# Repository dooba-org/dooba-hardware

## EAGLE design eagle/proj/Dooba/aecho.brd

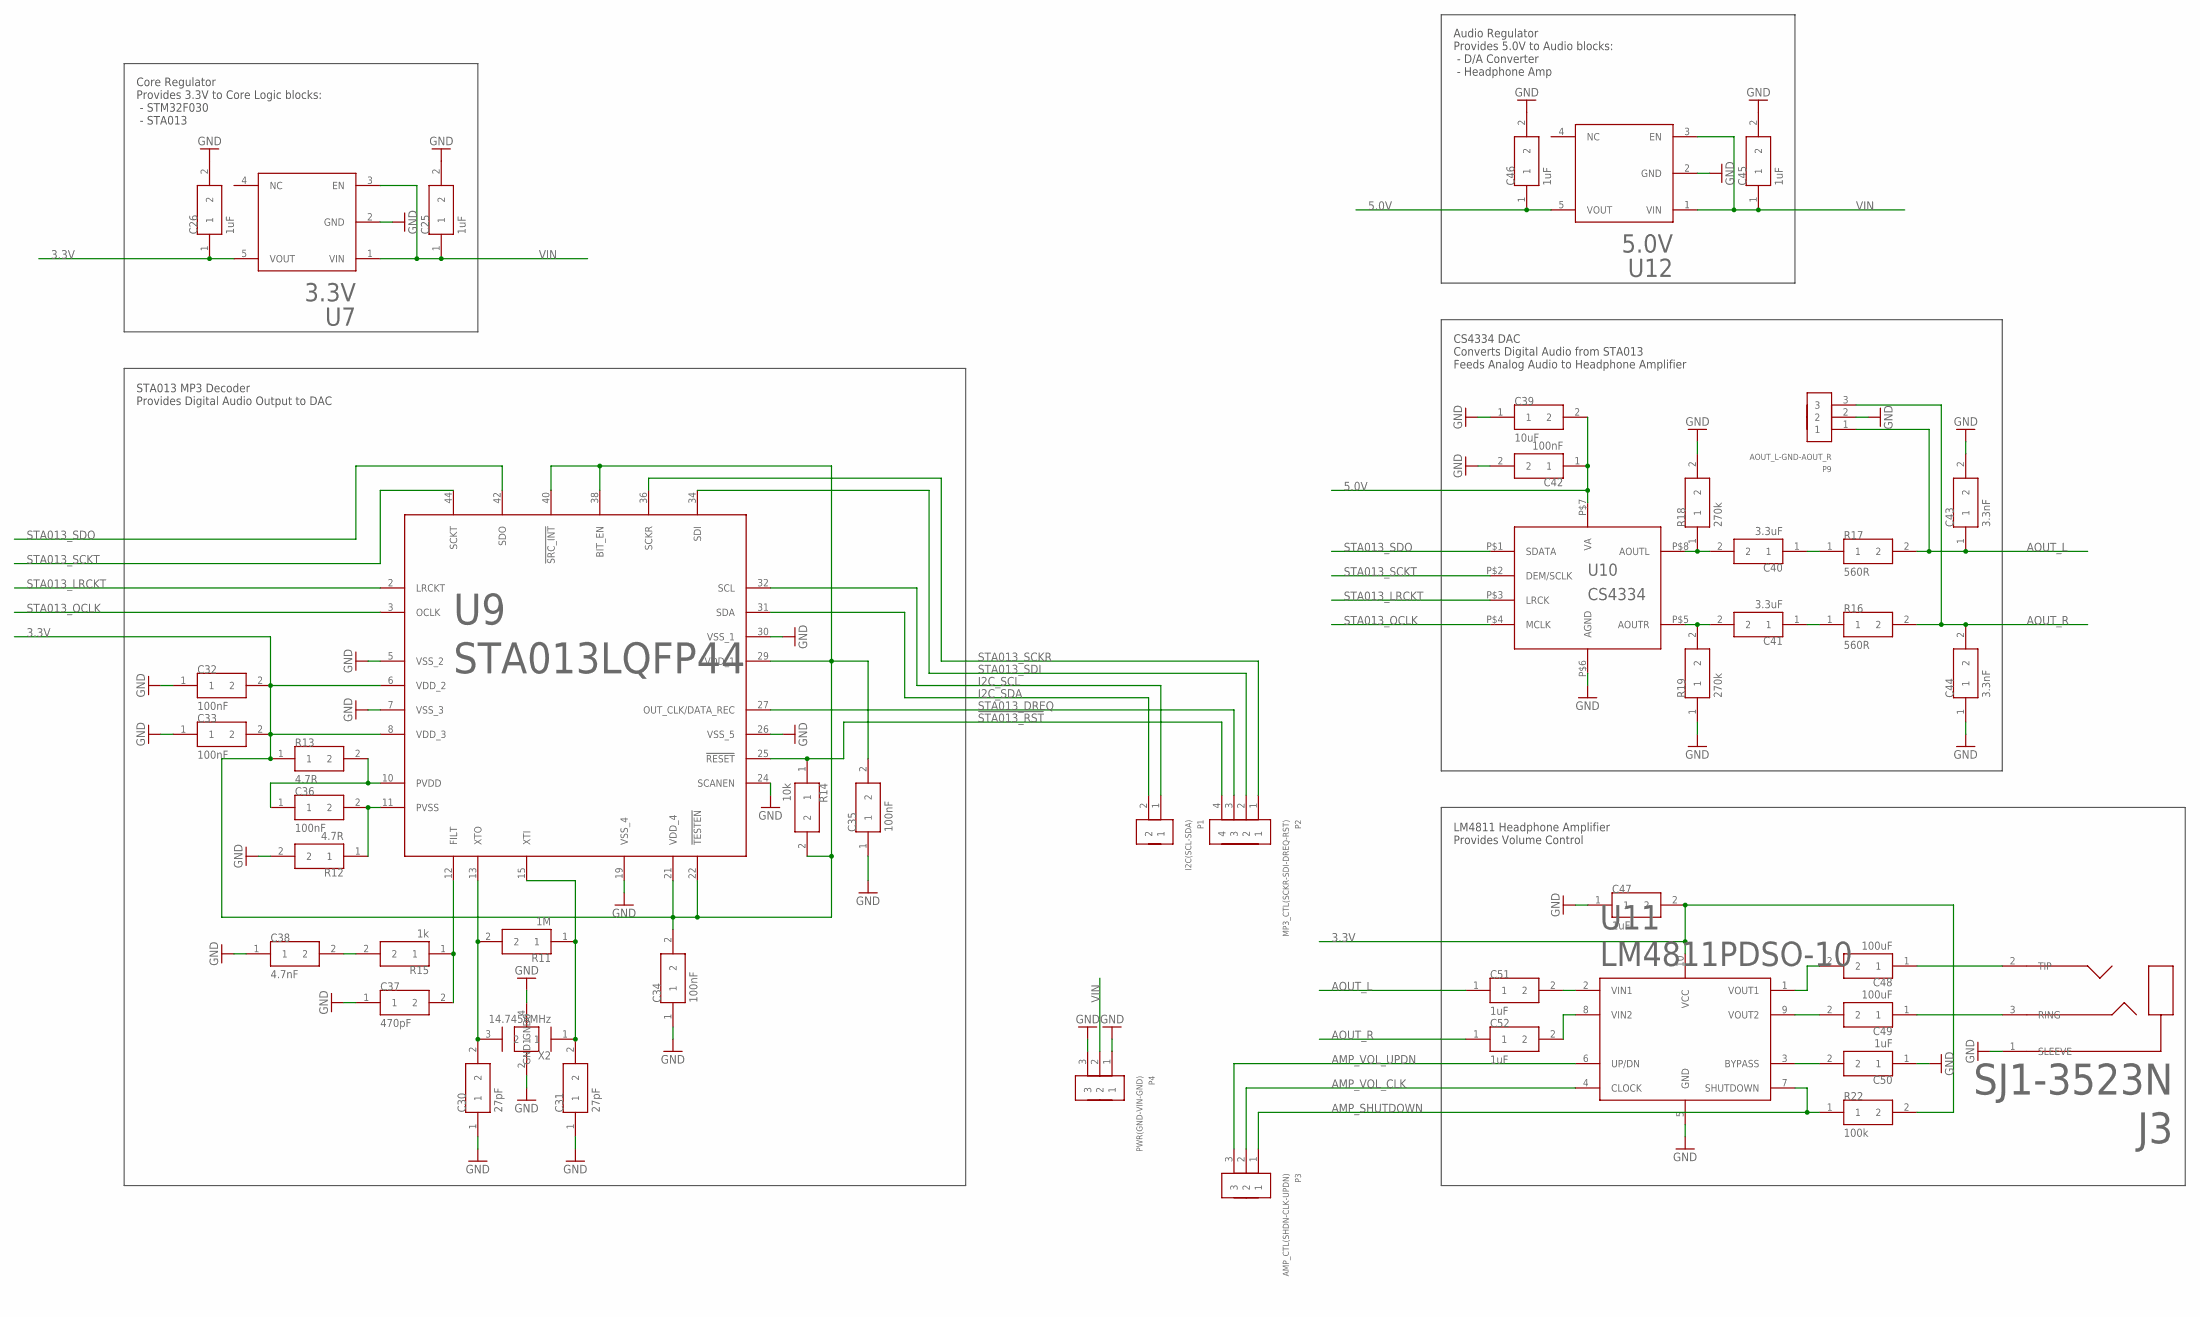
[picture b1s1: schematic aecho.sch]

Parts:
C25, C26, C45, C46, C47, C50, C51, C52: 1uF; 0805
C30, C31: 27pF; 0805
C32, C33, C34, C35, C36, C42: 100nF; 0805
C37: 470pF; 0805
C38: 4.7nF; 0805
C39: 10uF; 0805
C40, C41: 3.3uF; 0805
C43, C44: 3.3nF; 0805
C48, C49: 100uF; 1210
J3: SJ1-3523N; SJ1-352XN
P1: I2C(SCL-SDA); PIN_2
P2: MP3_CTL(SCKR-SDI-DREQ-RST); PIN_4
P3: AMP_CTL(SHDN-CLK-UPDN); PIN_3
P4: PWR(GND-VIN-GND); PIN_3
P9: AOUT_L-GND-AOUT_R; PIN_3
R11: 1M; 0805
R12, R13: 4.7R; 0805
R14: 10k; 0805
R15: 1k; 0805
R16, R17: 560R; 0805
R18, R19: 270k; 0805
R22: 100k; 0805
U7: 3.3V; SOT23-5
U9: STA013LQFP44; QFP44
U10: CS4334; SO8
U11: LM4811PDSO-10; PDSO-10
U12: 5.0V; SOT23-5
X2: 14.7456MHz; XTAL_3225

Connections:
3.3V: C26.1, C32.2, C33.2, C34.2, C35.2, C47.2, R13.1, R14.2, R22.2, U7.5 (VOUT), U9.6 (VDD_2), U9.8 (VDD_3), U9.21 (VDD_4), U9.22 (!TESTEN), U9.29 (VDD_1), U9.38 (BIT_EN), U9.40 (!SRC_INT), U11.10 (VCC)
5.0V: C39.2, C42.1, C46.1, U10.P$7 (VA), U12.5 (VOUT)
!STA013_RST: P2.4, R14.1, U9.25 (!RESET)
AMP_SHUTDOWN: P3.1, R22.1, U11.7 (SHUTDOWN)
AMP_VOL_CLK: P3.2, U11.4 (CLOCK)
AMP_VOL_UPDN: P3.3, U11.6 (UP/DN)
AOUT_L: C43.1, C51.1, P9.1, R17.2
AOUT_R: C44.2, C52.1, P9.3, R16.2
GND: C25.2, C26.2, C30.1, C31.1, C32.1, C33.1, C34.1, C35.1, C37.1, C38.1, C39.1, C42.2, C43.2, C44.1, C45.2, C46.2, C47.1, C50.1, J3.1 (SLEEVE), P4.1, P4.3, P9.2, R12.2, R18.2, R19.1, U7.2 (GND), U9.5 (VSS_2), U9.7 (VSS_3), U9.19 (VSS_4), U9.24 (SCANEN), U9.26 (VSS_5), U9.30 (VSS_1), U10.P$6 (AGND), U11.5 (GND), U12.2 (GND), X2.2 (GND0), X2.4 (GND1)
I2C_SCL: P1.1, U9.32 (SCL)
I2C_SDA: P1.2, U9.31 (SDA)
unnamed: C31.2, R11.1, U9.15 (XTI), X2.1
unnamed: C30.2, R11.2, U9.13 (XTO), X2.3 (2)
unnamed: C36.1, R13.2, U9.10 (PVDD)
unnamed: C36.2, R12.1, U9.11 (PVSS)
unnamed: C48.1, J3.2 (TIP)
unnamed: C38.2, R15.2
unnamed: C40.2, R18.1, U10.P$8 (AOUTL)
unnamed: C37.2, R15.1, U9.12 (FILT)
unnamed: C41.2, R19.2, U10.P$5 (AOUTR)
unnamed: C41.1, R16.1
unnamed: C40.1, R17.1
unnamed: C48.2, U11.1 (VOUT1)
unnamed: C49.2, U11.9 (VOUT2)
unnamed: C50.2, U11.3 (BYPASS)
unnamed: C49.1, J3.3 (RING)
unnamed: C51.2, U11.2 (VIN1)
unnamed: C52.2, U11.8 (VIN2)
STA013_DREQ: P2.3, U9.27 (OUT_CLK/DATA_REC)
STA013_LRCKT: U9.2 (LRCKT), U10.P$3 (LRCK)
STA013_OCLK: U9.3 (OCLK), U10.P$4 (MCLK)
STA013_SCKR: P2.1, U9.36 (SCKR)
STA013_SCKT: U9.44 (SCKT), U10.P$2 (DEM/SCLK)
STA013_SDI: P2.2, U9.34 (SDI)
STA013_SDO: U9.42 (SDO), U10.P$1 (SDATA)
VIN: C25.1, C45.1, P4.2, U7.1 (VIN), U7.3 (EN), U12.1 (VIN), U12.3 (EN)

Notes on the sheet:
Core Regulator Provides 3.3V to Core Logic blocks: - STM32F030 - STA013
STA013 MP3 Decoder Provides Digital Audio Output to DAC
CS4334 DAC Converts Digital Audio from STA013 Feeds Analog Audio to Headphone Amplifier
Audio Regulator Provides 5.0V to Audio blocks: - D/A Converter - Headphone Amp
LM4811 Headphone Amplifier Provides Volume Control

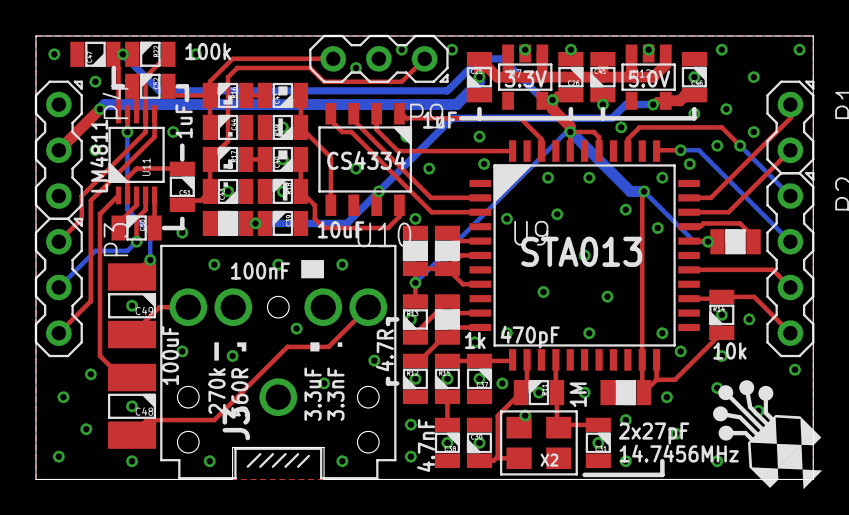
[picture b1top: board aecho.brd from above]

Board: 2 copper layers, 43.2 x 24.6 mm, 47 parts (0 on the bottom side), 36 nets.

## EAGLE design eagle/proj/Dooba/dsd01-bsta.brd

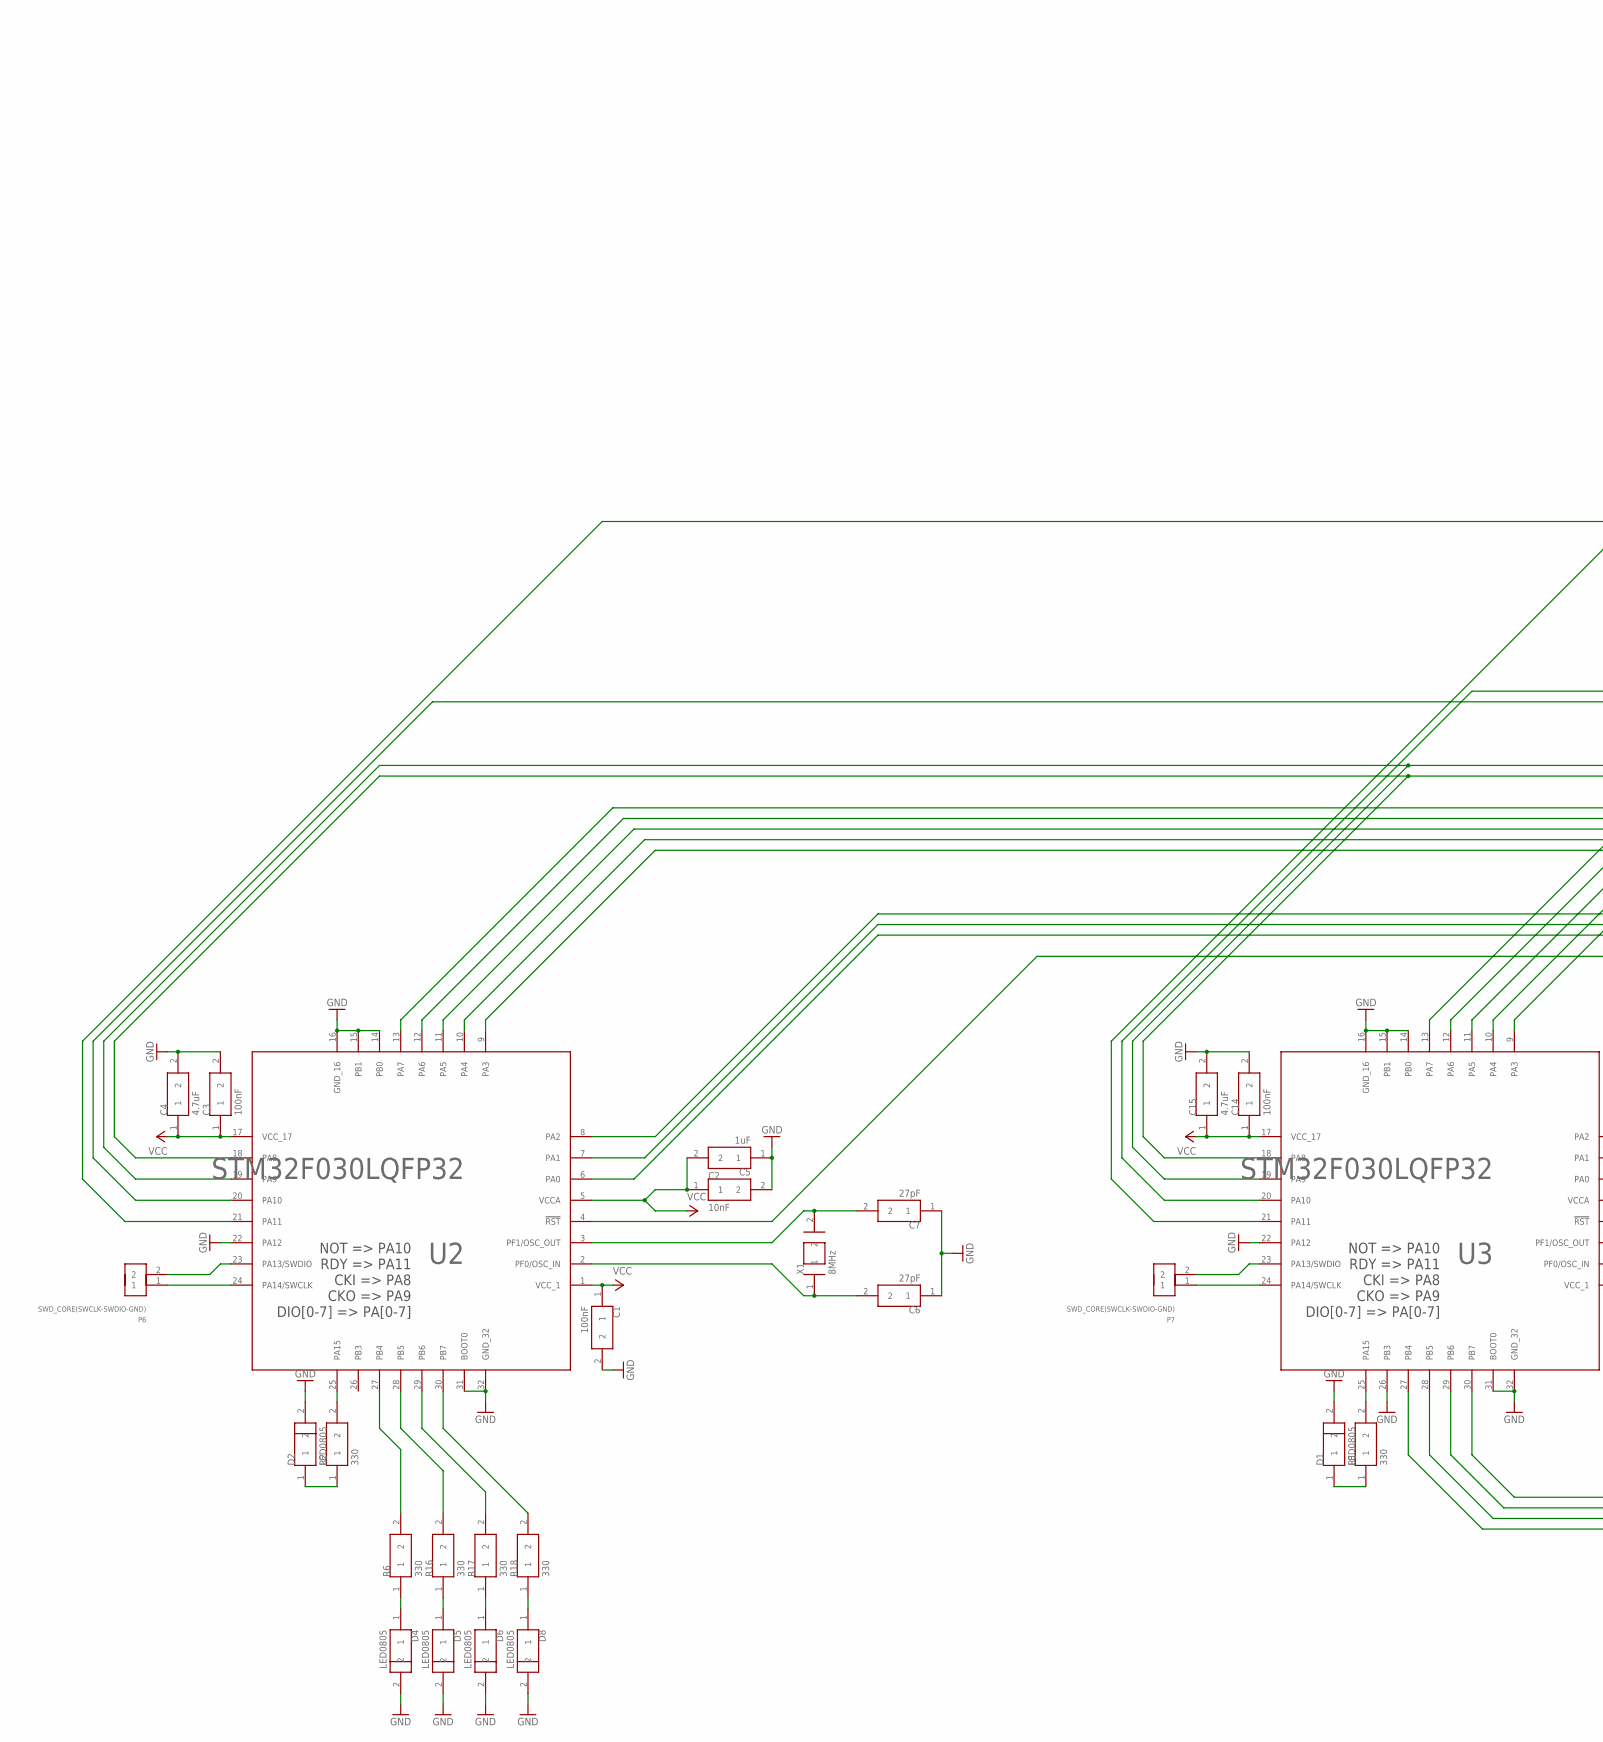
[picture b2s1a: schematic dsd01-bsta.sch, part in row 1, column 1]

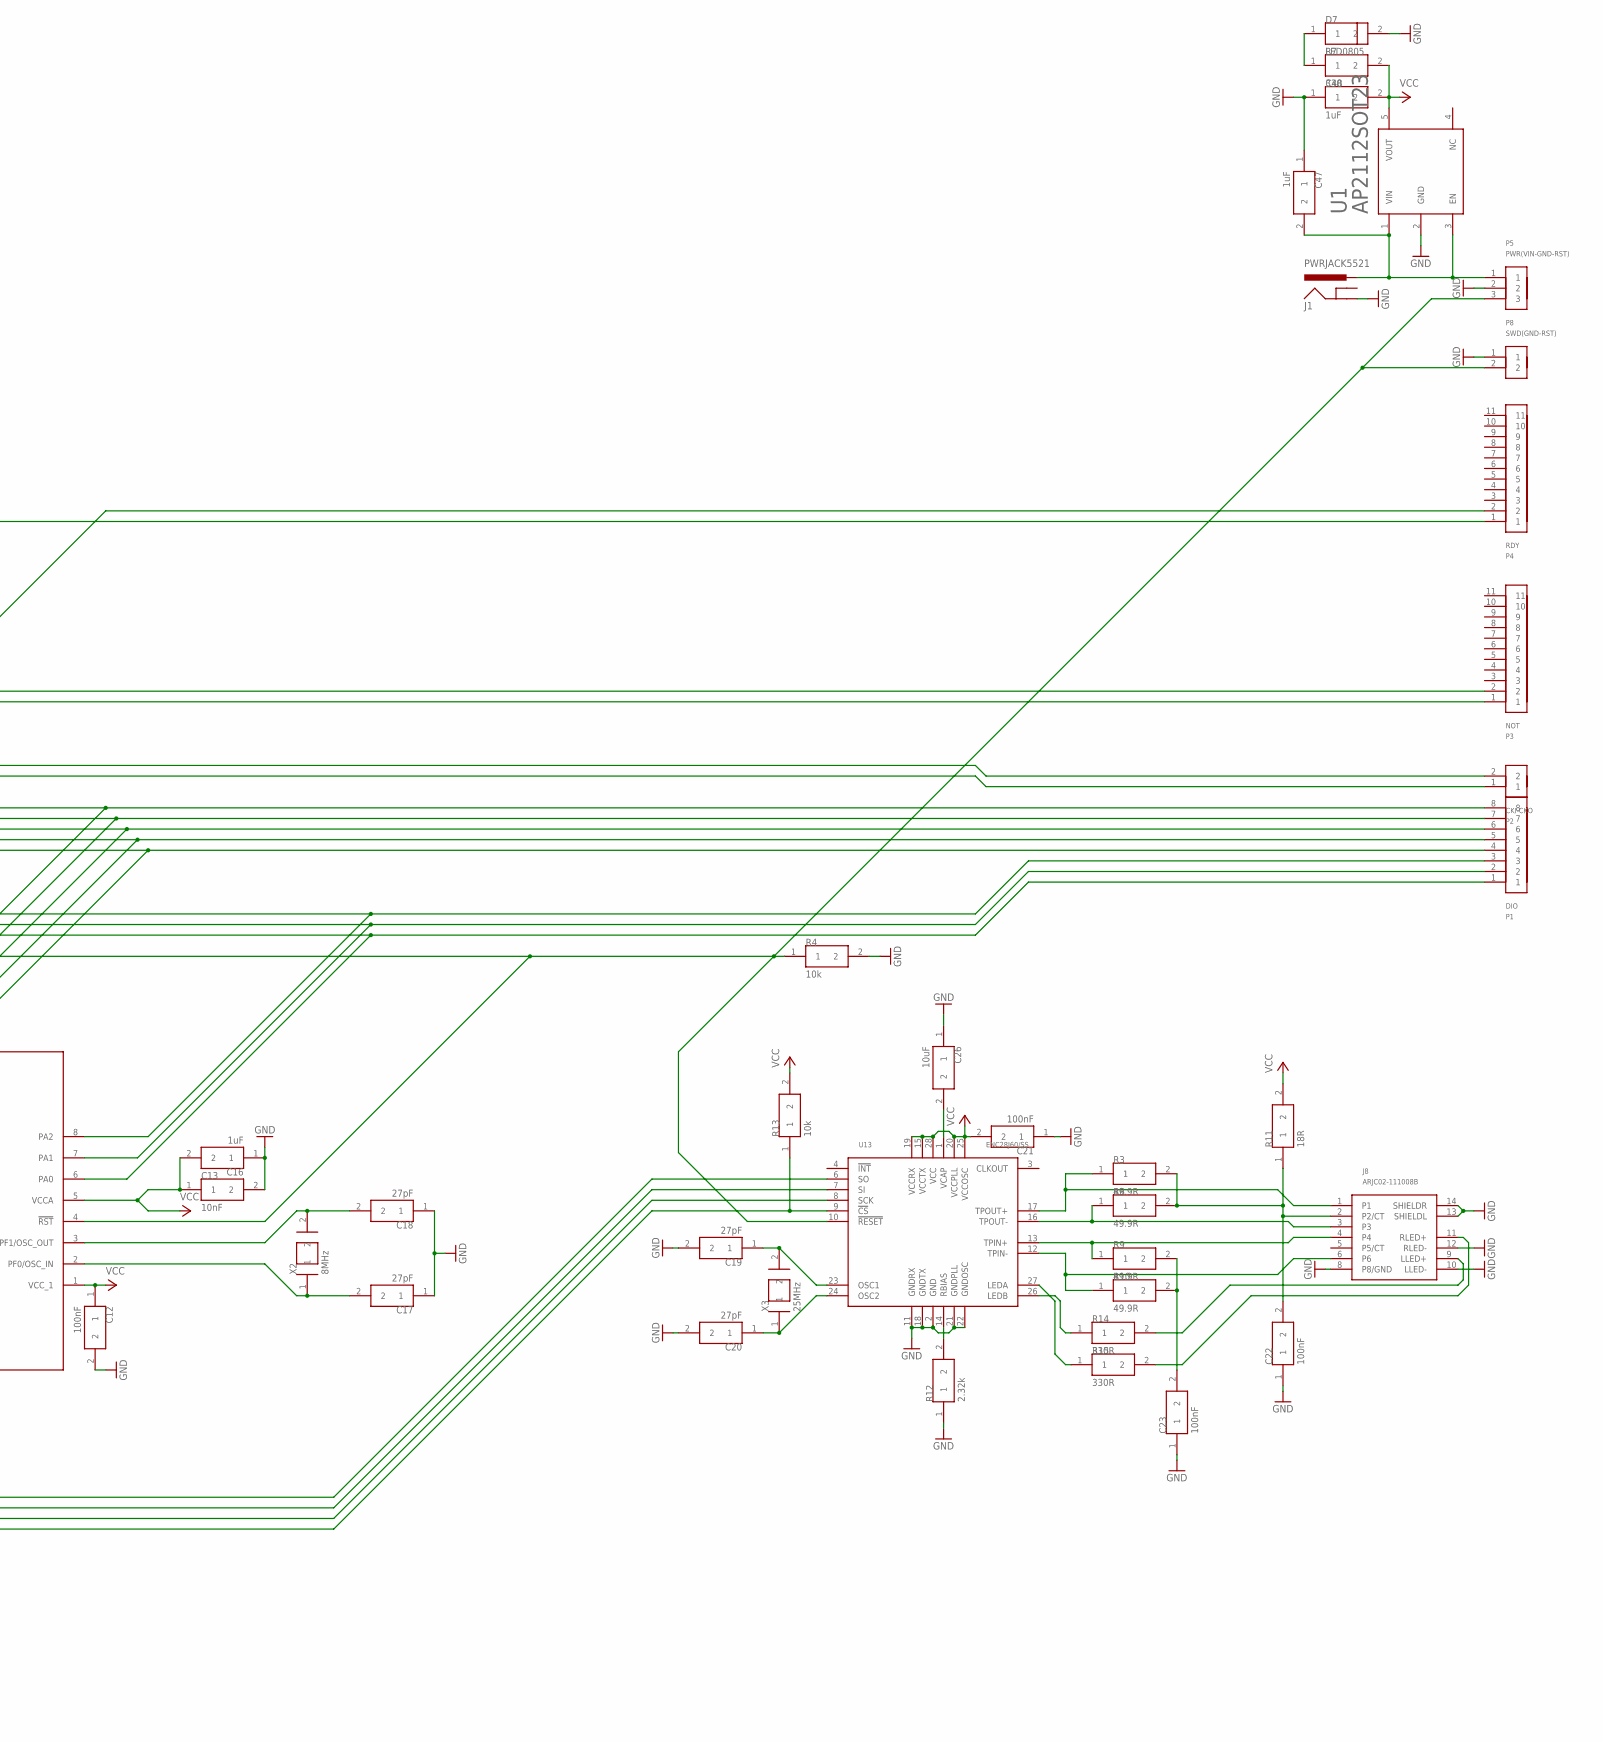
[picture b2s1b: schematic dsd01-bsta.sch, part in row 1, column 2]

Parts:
C1, C3, C12, C14, C21, C22, C23: 100nF; 0805
C2, C13: 10nF; 0805
C4, C15: 4.7uF; 0805
C5, C16, C47, C48: 1uF; 0805
C6, C7, C17, C18, C19, C20: 27pF; 0805
C26: 10uF; 0805
D1, D2, D4, D5, D6, D7, D8: LED0805; 0805
J1: PWRJACK5521; PWRJACK_5521
J8: ARJC02-111008B
P1: DIO; PIN_8
P2: CKI-CKO; PIN_2
P3: NOT; PIN_11
P4: RDY; PIN_11
P5: PWR(VIN-GND-RST); PIN_3
P6, P7: SWD_CORE(SWCLK-SWDIO-GND); PIN_2
P8: SWD(GND-RST); PIN_2
R1, R2, R6, R7, R16, R17, R18: 330; 0805
R3, R8, R9, R10: 49.9R; 0805
R4, R13: 10k; 0805
R11: 18R; 0805
R12: 2.32k; 0805
R14, R15: 330R; 0805
U1: AP2112SOT23; SOT23-5
U2, U3: STM32F030LQFP32; QFP32
U13: ENC28J60/SS; SSOP28
X1, X2: 8MHz; XTAL_532
X3: 25MHz; XTAL_532

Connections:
GND: C1.2, C2.2, C3.2, C4.2, C5.1, C6.1, C7.1, C12.2, C13.2, C14.2, C15.2, C16.1, C17.1, C18.1, C19.2, C20.2, C21.1, C22.1, C23.1, C26.1, C47.1, C48.1, D1.2, D2.2, D4.2, D5.2, D6.2, D7.2, D8.2, J1.GND, J8.8 (P8/GND), J8.10 (LLED-), J8.12 (RLED-), J8.13 (SHIELDL), J8.14 (SHIELDR), P5.2, P8.1, R4.2, R12.1, U1.2 (GND), U2.14 (PB0), U2.15 (PB1), U2.16 (GND_16), U2.22 (PA12), U2.31 (BOOT0), U2.32 (GND_32), U3.14 (PB0), U3.15 (PB1), U3.16 (GND_16), U3.22 (PA12), U3.26 (PB3), U3.31 (BOOT0), U3.32 (GND_32), U13.2 (GND), U13.11 (GNDRX), U13.18 (GNDTX), U13.21 (GNDPLL), U13.22 (GNDOSC)
unnamed: C47.2, J1.PWR, P5.1, U1.1 (VIN), U1.3 (EN)
unnamed: C6.2, U2.2 (PF0/OSC_IN), X1.1
unnamed: C7.2, U2.3 (PF1/OSC_OUT), X1.2
unnamed: P3.1, U2.20 (PA10)
unnamed: P4.1, U2.21 (PA11)
unnamed: P1.2, U2.7 (PA1), U3.7 (PA1)
unnamed: P1.3, U2.8 (PA2), U3.8 (PA2)
unnamed: P1.4, U2.9 (PA3), U3.9 (PA3)
unnamed: P1.5, U2.10 (PA4), U3.10 (PA4)
unnamed: P1.6, U2.11 (PA5), U3.11 (PA5)
unnamed: P1.7, U2.12 (PA6), U3.12 (PA6)
unnamed: P1.8, U2.13 (PA7), U3.13 (PA7)
unnamed: P2.2, U2.19 (PA9), U3.19 (PA9)
unnamed: P2.1, U2.18 (PA8), U3.18 (PA8)
unnamed: P1.1, U2.6 (PA0), U3.6 (PA0)
unnamed: P6.2, U2.23 (PA13/SWDIO)
unnamed: P6.1, U2.24 (PA14/SWCLK)
unnamed: D2.1, R2.1
unnamed: R2.2, U2.25 (PA15)
unnamed: U3.30 (PB7), U13.6 (SO)
unnamed: U3.29 (PB6), U13.7 (SI)
unnamed: U3.28 (PB5), U13.8 (SCK)
unnamed: P5.3, P8.2, R4.1, U2.4 (!RST), U3.4 (!RST), U13.10 (!RESET)
unnamed: C22.2, J8.2 (P2/CT), R3.2, R8.2, R11.1
unnamed: R15.1, U13.27 (LEDA)
unnamed: R14.1, U13.26 (LEDB)
unnamed: J8.9 (LLED+), R14.2
unnamed: J8.11 (RLED+), R15.2
unnamed: R6.2, U2.27 (PB4)
unnamed: R16.2, U2.28 (PB5)
unnamed: C17.2, U3.2 (PF0/OSC_IN), X2.1
unnamed: C18.2, U3.3 (PF1/OSC_OUT), X2.2
unnamed: R17.2, U2.29 (PB6)
unnamed: R18.2, U2.30 (PB7)
unnamed: D4.1, R6.1
unnamed: D5.1, R16.1
unnamed: D6.1, R17.1
unnamed: D8.1, R18.1
unnamed: P7.2, U3.23 (PA13/SWDIO)
unnamed: P4.2, U3.21 (PA11)
unnamed: P7.1, U3.24 (PA14/SWCLK)
unnamed: D1.1, R1.1
unnamed: R1.2, U3.25 (PA15)
unnamed: C26.2, U13.1 (VCAP)
unnamed: R12.2, U13.14 (RBIAS)
unnamed: C20.1, U13.24 (OSC2), X3.1
unnamed: C19.1, U13.23 (OSC1), X3.2
unnamed: J8.4, R9.1, U13.13 (TPIN+)
unnamed: J8.6, R10.1, U13.12 (TPIN-)
unnamed: C23.2, R9.2, R10.2
unnamed: J8.1, R3.1, U13.17 (TPOUT+)
unnamed: J8.3, R8.1, U13.16 (TPOUT-)
unnamed: R13.1, U3.27 (PB4), U13.9 (!CS)
unnamed: P3.2, U3.20 (PA10)
unnamed: D7.1, R7.1
VCC: C1.1, C2.1, C3.1, C4.1, C5.2, C12.1, C13.1, C14.1, C15.1, C16.2, C21.2, C48.2, R7.2, R11.2, R13.2, U1.5 (VOUT), U2.1 (VCC_1), U2.5 (VCCA), U2.17 (VCC_17), U3.1 (VCC_1), U3.5 (VCCA), U3.17 (VCC_17), U13.15 (VCCTX), U13.19 (VCCRX), U13.20 (VCCPLL), U13.25 (VCCOSC), U13.28 (VCC)

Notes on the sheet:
NOT => PA10 RDY => PA11 CKI => PA8 CKO => PA9 DIO[0-7] => PA[0-7]

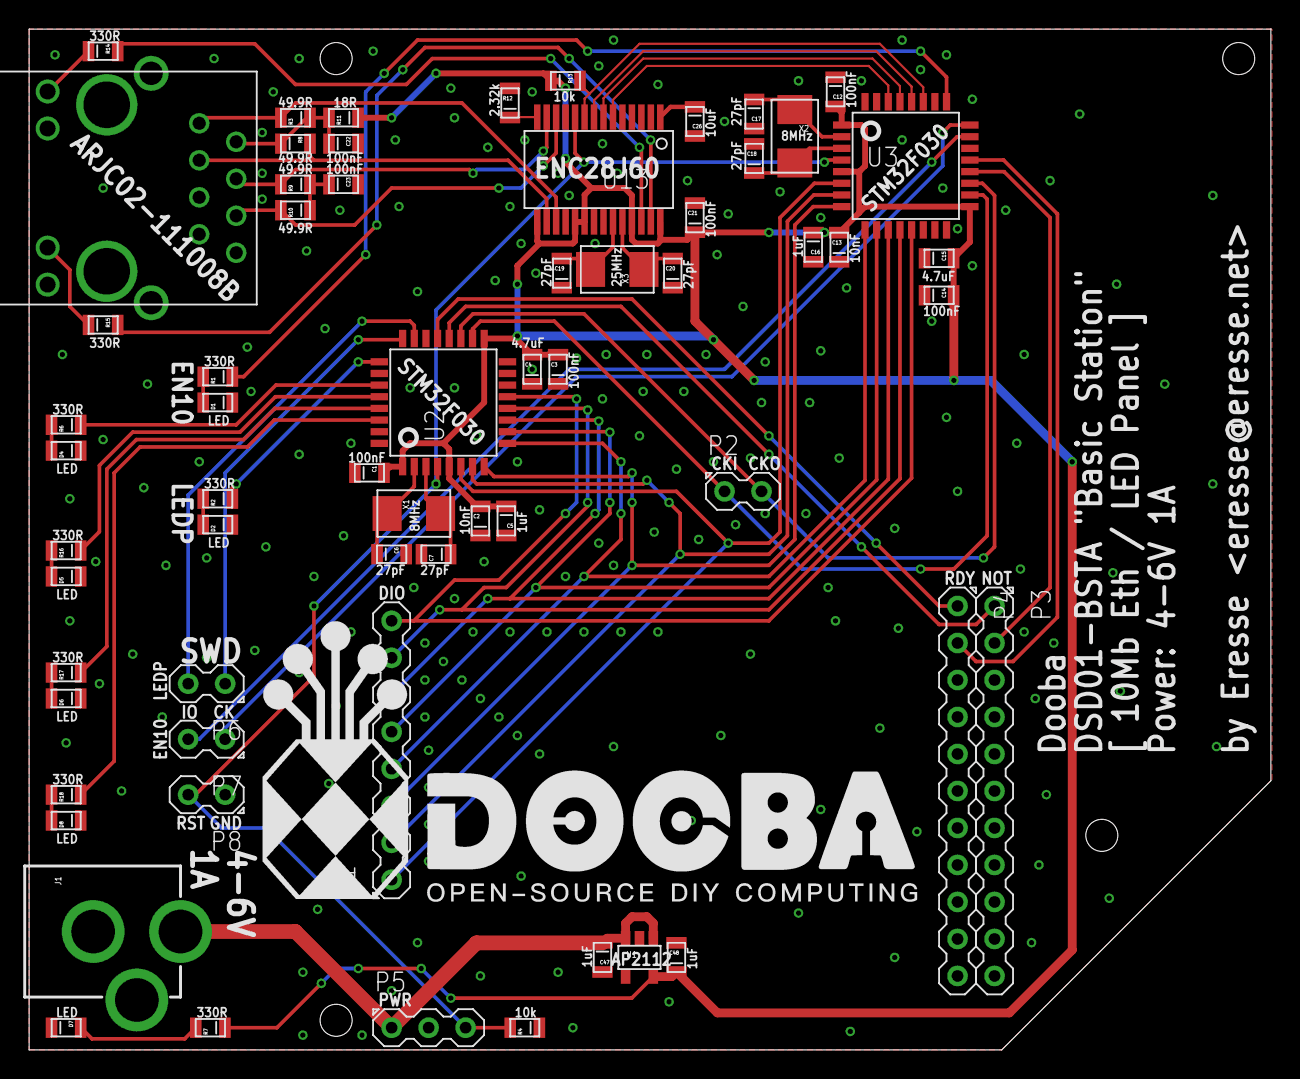
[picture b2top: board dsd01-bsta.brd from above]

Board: 2 copper layers, 85.3 x 70.1 mm, 63 parts (0 on the bottom side), 57 nets.

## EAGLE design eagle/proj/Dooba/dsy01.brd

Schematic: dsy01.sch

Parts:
C1, C2, C17, C18, C31, C32, C38, C39, C45, C46, C54, C55: 27pF; 0805
C3, C4, C5, C7, C8, C12, C14, C26, C28, C33, C35, C40, C42, C49, C51, C56: 100nF; 0805
C6, C13, C27, C34, C41, C50: 10nF; 0805
C9, C16, C30, C37, C44, C47, C48, C53: 1uF; 0805
C10, C11, C15, C29, C36, C43, C52: 4.7uF; 0805
D1, D2, D3, D4, D5, D6, D7: LED0805; 0805
P1: DIO; PIN_8
P2: CKI-CKO; PIN_2
P3: NOT; PIN_11
P4: RDY; PIN_11
P5: PWR(VIN-GND-RST); PIN_3
P6, P7, P8, P9, P10, P11: SWD_CORE(SWCLK-SWDIO-GND); PIN_2
P12: SWD(GND-RST); PIN_2
R1, R2, R3, R4, R5, R6, R7: 330; 0805
U1: STM32F071LQFP100; QFP100
U2: AS6C1608TSOPII-44; TSOPII-44
U3, U5, U6, U7, U9: STM32F030LQFP32; QFP32
U8: AP2112SOT23; SOT23-5
U10: S25FLXXXSSOIC16; SO3-016
X1, X2, X4, X5, X6, X7: 8MHz; XTAL_532

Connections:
GND: C1.1, C2.1, C3.1, C4.1, C5.2, C6.1, C7.2, C8.1, C9.1, C10.1, C11.1, C12.2, C13.2, C14.2, C15.2, C16.1, C17.1, C18.1, C26.2, C27.2, C28.2, C29.2, C30.1, C31.1, C32.1, C33.2, C34.2, C35.2, C36.2, C37.1, C38.1, C39.1, C40.2, C41.2, C42.2, C43.2, C44.1, C45.1, C46.1, C47.1, C48.1, C49.2, C50.2, C51.2, C52.2, C53.1, C54.1, C55.1, C56.1, D1.2, D2.2, D3.2, D4.2, D5.2, D6.2, D7.2, P5.2, P12.1, U1.5 (PE6), U1.11 (PF10), U1.19 (PF2), U1.20 (GNDA_20), U1.22 (PF3), U1.27 (GND_27), U1.38 (PE7), U1.49 (GND_49), U1.73 (PF6), U1.74 (GND_74), U1.77 (PA15), U1.94 (BOOT0), U1.99 (GND_99), U2.12 (GND_12), U2.34 (GND_34), U3.14 (PB0), U3.15 (PB1), U3.16 (GND_16), U3.22 (PA12), U3.26 (PB3), U3.27 (PB4), U3.28 (PB5), U3.29 (PB6), U3.30 (PB7), U3.31 (BOOT0), U3.32 (GND_32), U5.14 (PB0), U5.15 (PB1), U5.16 (GND_16), U5.22 (PA12), U5.26 (PB3), U5.27 (PB4), U5.28 (PB5), U5.29 (PB6), U5.30 (PB7), U5.31 (BOOT0), U5.32 (GND_32), U6.14 (PB0), U6.15 (PB1), U6.16 (GND_16), U6.22 (PA12), U6.26 (PB3), U6.27 (PB4), U6.28 (PB5), U6.29 (PB6), U6.30 (PB7), U6.31 (BOOT0), U6.32 (GND_32), U7.14 (PB0), U7.15 (PB1), U7.16 (GND_16), U7.22 (PA12), U7.26 (PB3), U7.27 (PB4), U7.28 (PB5), U7.29 (PB6), U7.30 (PB7), U7.31 (BOOT0), U7.32 (GND_32), U8.2 (GND), U9.14 (PB0), U9.15 (PB1), U9.16 (GND_16), U9.22 (PA12), U9.26 (PB3), U9.31 (BOOT0), U9.32 (GND_32), U10.10 (GND)
unnamed: C1.2, U1.12 (PF0/OSC_IN), X1.1
unnamed: C2.2, U1.13 (PF1/OSC_OUT), X1.2
unnamed: U1.55 (PD8), U2.39 (A8)
unnamed: U1.32 (PA7), U2.36 (DQ7)
unnamed: U1.31 (PA6), U2.35 (DQ6)
unnamed: U1.30 (PA5), U2.32 (DQ5)
unnamed: U1.29 (PA4), U2.31 (DQ4)
unnamed: U1.26 (PA3), U2.14 (DQ3)
unnamed: U1.25 (PA2), U2.13 (DQ2)
unnamed: U1.24 (PA1), U2.10 (DQ1)
unnamed: U1.23 (PA0), U2.9 (DQ0)
unnamed: U1.56 (PD9), U2.28 (A9)
unnamed: U1.57 (PD10), U2.27 (A10)
unnamed: U1.58 (PD11), U2.26 (A11)
unnamed: U1.59 (PD12), U2.25 (A12)
unnamed: U1.60 (PD13), U2.24 (A13)
unnamed: U1.61 (PD14), U2.23 (A14)
unnamed: U1.62 (PD15), U2.22 (A15)
unnamed: U1.67 (PA8), U2.21 (A16)
unnamed: U1.68 (PA9), U2.20 (A17)
unnamed: U1.69 (PA10), U2.19 (A18)
unnamed: U1.70 (PA11), U2.18 (A19)
unnamed: U1.71 (PA12), U2.16 (A20)
unnamed: U1.81 (PD0), U2.5 (A0)
unnamed: U1.82 (PD1), U2.4 (A1)
unnamed: U1.83 (PD2), U2.3 (A2)
unnamed: U1.84 (PD3), U2.2 (A3)
unnamed: U1.85 (PD4), U2.1 (A4)
unnamed: U1.86 (PD5), U2.44 (A5)
unnamed: U1.87 (PD6), U2.43 (A6)
unnamed: U1.88 (PD7), U2.42 (A7)
unnamed: C17.2, U3.2 (PF0/OSC_IN), X2.1
unnamed: C18.2, U3.3 (PF1/OSC_OUT), X2.2
unnamed: C47.2, P5.1, U8.1 (VIN), U8.3 (EN)
unnamed: P5.3, P12.2, U1.14 (!RST), U3.4 (!RST), U5.4 (!RST), U6.4 (!RST), U7.4 (!RST), U9.4 (!RST)
unnamed: U1.1 (PE2), U2.41 (!OE)
unnamed: U1.2 (PE3), U2.17 (!WE)
unnamed: U1.3 (PE4), U2.40 (CE2)
unnamed: U1.4 (PE5), U2.6 (!CE)
unnamed: P6.1, U1.76 (PA14/SWCLK)
unnamed: P6.2, U1.72 (PA13/SWDIO)
unnamed: P7.2, U3.23 (PA13/SWDIO)
unnamed: U9.29 (PB6), U10.16 (SCK)
unnamed: U1.15 (PC0), U3.21 (PA11)
unnamed: P10.1, U7.24 (PA14/SWCLK)
unnamed: P8.2, U5.23 (PA13/SWDIO)
unnamed: P9.1, U6.24 (PA14/SWCLK)
unnamed: P9.2, U6.23 (PA13/SWDIO)
unnamed: P8.1, U5.24 (PA14/SWCLK)
unnamed: P10.2, U7.23 (PA13/SWDIO)
unnamed: P7.1, U3.24 (PA14/SWCLK)
unnamed: P11.2, U9.23 (PA13/SWDIO)
unnamed: P11.1, U9.24 (PA14/SWCLK)
unnamed: D1.1, R1.1
unnamed: P1.2, U1.40 (PE9), U3.7 (PA1), U5.7 (PA1), U6.7 (PA1), U7.7 (PA1), U9.7 (PA1)
unnamed: R1.2, U3.25 (PA15)
unnamed: P3.5, U1.96 (PB9)
unnamed: P3.4, U1.95 (PB8)
unnamed: P3.3, U1.93 (PB7)
unnamed: P3.2, U1.92 (PB6)
unnamed: P3.1, U1.91 (PB5)
unnamed: D2.1, R2.1
unnamed: P1.3, U1.41 (PE10), U3.8 (PA2), U5.8 (PA2), U6.8 (PA2), U7.8 (PA2), U9.8 (PA2)
unnamed: P3.6, U1.47 (PB10)
unnamed: P3.7, U1.48 (PB11)
unnamed: P3.8, U1.51 (PB12)
unnamed: P3.9, U1.52 (PB13)
unnamed: P3.10, U1.53 (PB14)
unnamed: P3.11, U1.54 (PB15)
unnamed: R2.2, U5.25 (PA15)
unnamed: P1.4, U1.42 (PE11), U3.9 (PA3), U5.9 (PA3), U6.9 (PA3), U7.9 (PA3), U9.9 (PA3)
unnamed: P1.5, U1.43 (PE12), U3.10 (PA4), U5.10 (PA4), U6.10 (PA4), U7.10 (PA4), U9.10 (PA4)
unnamed: P1.6, U1.44 (PE13), U3.11 (PA5), U5.11 (PA5), U6.11 (PA5), U7.11 (PA5), U9.11 (PA5)
unnamed: D3.1, R3.1
unnamed: P4.1, U1.34 (PC5)
unnamed: P4.2, U1.63 (PC6)
unnamed: P4.3, U1.64 (PC7)
unnamed: P4.4, U1.65 (PC8)
unnamed: P4.5, U1.66 (PC9)
unnamed: P4.8, U1.80 (PC12)
unnamed: P4.7, U1.79 (PC11)
unnamed: P4.6, U1.78 (PC10)
unnamed: P4.9, U1.7 (PC13)
unnamed: P4.10, U1.8 (PC14/OSC32_IN)
unnamed: P4.11, U1.9 (PC15/OSC32_OUT)
unnamed: U1.35 (PB0), U3.20 (PA10)
unnamed: R3.2, U6.25 (PA15)
unnamed: D4.1, R4.1
unnamed: R4.2, U7.25 (PA15)
unnamed: C31.2, U5.2 (PF0/OSC_IN), X4.1
unnamed: C32.2, U5.3 (PF1/OSC_OUT), X4.2
unnamed: D5.1, R5.1
unnamed: P1.7, U1.45 (PE14), U3.12 (PA6), U5.12 (PA6), U6.12 (PA6), U7.12 (PA6), U9.12 (PA6)
unnamed: P1.8, U1.46 (PE15), U3.13 (PA7), U5.13 (PA7), U6.13 (PA7), U7.13 (PA7), U9.13 (PA7)
unnamed: P2.2, U1.98 (PE1), U3.19 (PA9), U5.19 (PA9), U6.19 (PA9), U7.19 (PA9), U9.19 (PA9)
unnamed: P2.1, U1.97 (PE0), U3.18 (PA8), U5.18 (PA8), U6.18 (PA8), U7.18 (PA8), U9.18 (PA8)
unnamed: P1.1, U1.39 (PE8), U3.6 (PA0), U5.6 (PA0), U6.6 (PA0), U7.6 (PA0), U9.6 (PA0)
unnamed: C54.2, U9.2 (PF0/OSC_IN), X7.1
unnamed: C55.2, U9.3 (PF1/OSC_OUT), X7.2
unnamed: U1.90 (PB4), U9.20 (PA10)
unnamed: U1.33 (PC4), U9.21 (PA11)
unnamed: U1.36 (PB1), U5.20 (PA10)
unnamed: U1.16 (PC1), U5.21 (PA11)
unnamed: C38.2, U6.2 (PF0/OSC_IN), X5.1
unnamed: C39.2, U6.3 (PF1/OSC_OUT), X5.2
unnamed: U9.30 (PB7), U10.15 (IO0/SI)
unnamed: U9.28 (PB5), U10.7 (!CS)
unnamed: U9.27 (PB4), U10.8 (IO1/SO)
unnamed: R5.2, U9.25 (PA15)
unnamed: D6.1, R6.1
unnamed: R6.2, U1.10 (PF9)
unnamed: D7.1, R7.1
unnamed: U1.37 (PB2), U6.20 (PA10)
unnamed: U1.17 (PC2), U6.21 (PA11)
unnamed: C45.2, U7.2 (PF0/OSC_IN), X6.1
unnamed: C46.2, U7.3 (PF1/OSC_OUT), X6.2
unnamed: U1.89 (PB3), U7.20 (PA10)
unnamed: U1.18 (PC3), U7.21 (PA11)
VCC: C3.2, C4.2, C5.1, C6.2, C7.1, C8.2, C9.2, C10.2, C11.2, C12.1, C13.1, C14.1, C15.1, C16.2, C26.1, C27.1, C28.1, C29.1, C30.2, C33.1, C34.1, C35.1, C36.1, C37.2, C40.1, C41.1, C42.1, C43.1, C44.2, C48.2, C49.1, C50.1, C51.1, C52.1, C53.2, C56.2, R7.2, U1.21 (VCCA_21), U1.28 (VCC_28), U1.50 (VCC_50), U1.75 (VCCIO2), U1.100 (VCC_100), U2.11 (VCC_11), U2.33 (VCC_33), U3.1 (VCC_1), U3.5 (VCCA), U3.17 (VCC_17), U5.1 (VCC_1), U5.5 (VCCA), U5.17 (VCC_17), U6.1 (VCC_1), U6.5 (VCCA), U6.17 (VCC_17), U7.1 (VCC_1), U7.5 (VCCA), U7.17 (VCC_17), U8.5 (VOUT), U9.1 (VCC_1), U9.5 (VCCA), U9.17 (VCC_17), U10.2 (VCC), U10.3 (RFU/!RST), U10.14 (VIO/RFU)

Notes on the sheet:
NOT[0-15] => PB RDY[0-15] => PC CKI => PE0 CKO => PE1 DIO[0-7] => PE[8-15]
NOT => PA10 RDY => PA11 CKI => PA8 CKO => PA9 DIO[0-7] => PA[0-7]

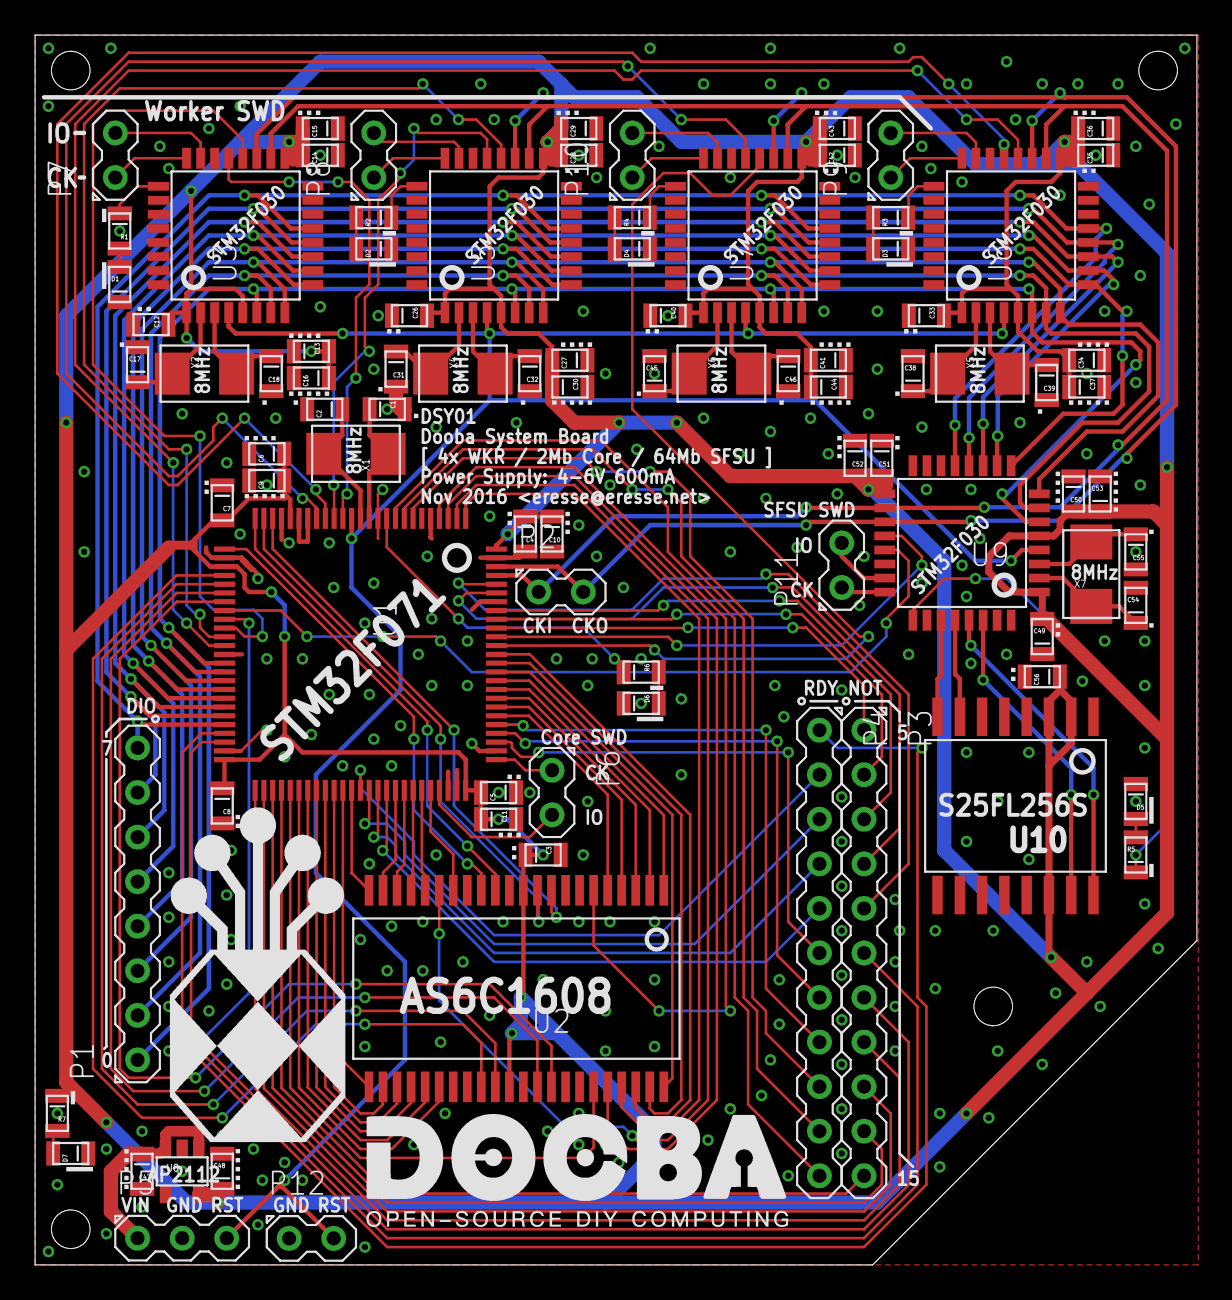
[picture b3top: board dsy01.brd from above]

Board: 2 copper layers, 66.2 x 70.1 mm, 90 parts (0 on the bottom side), 120 nets.
